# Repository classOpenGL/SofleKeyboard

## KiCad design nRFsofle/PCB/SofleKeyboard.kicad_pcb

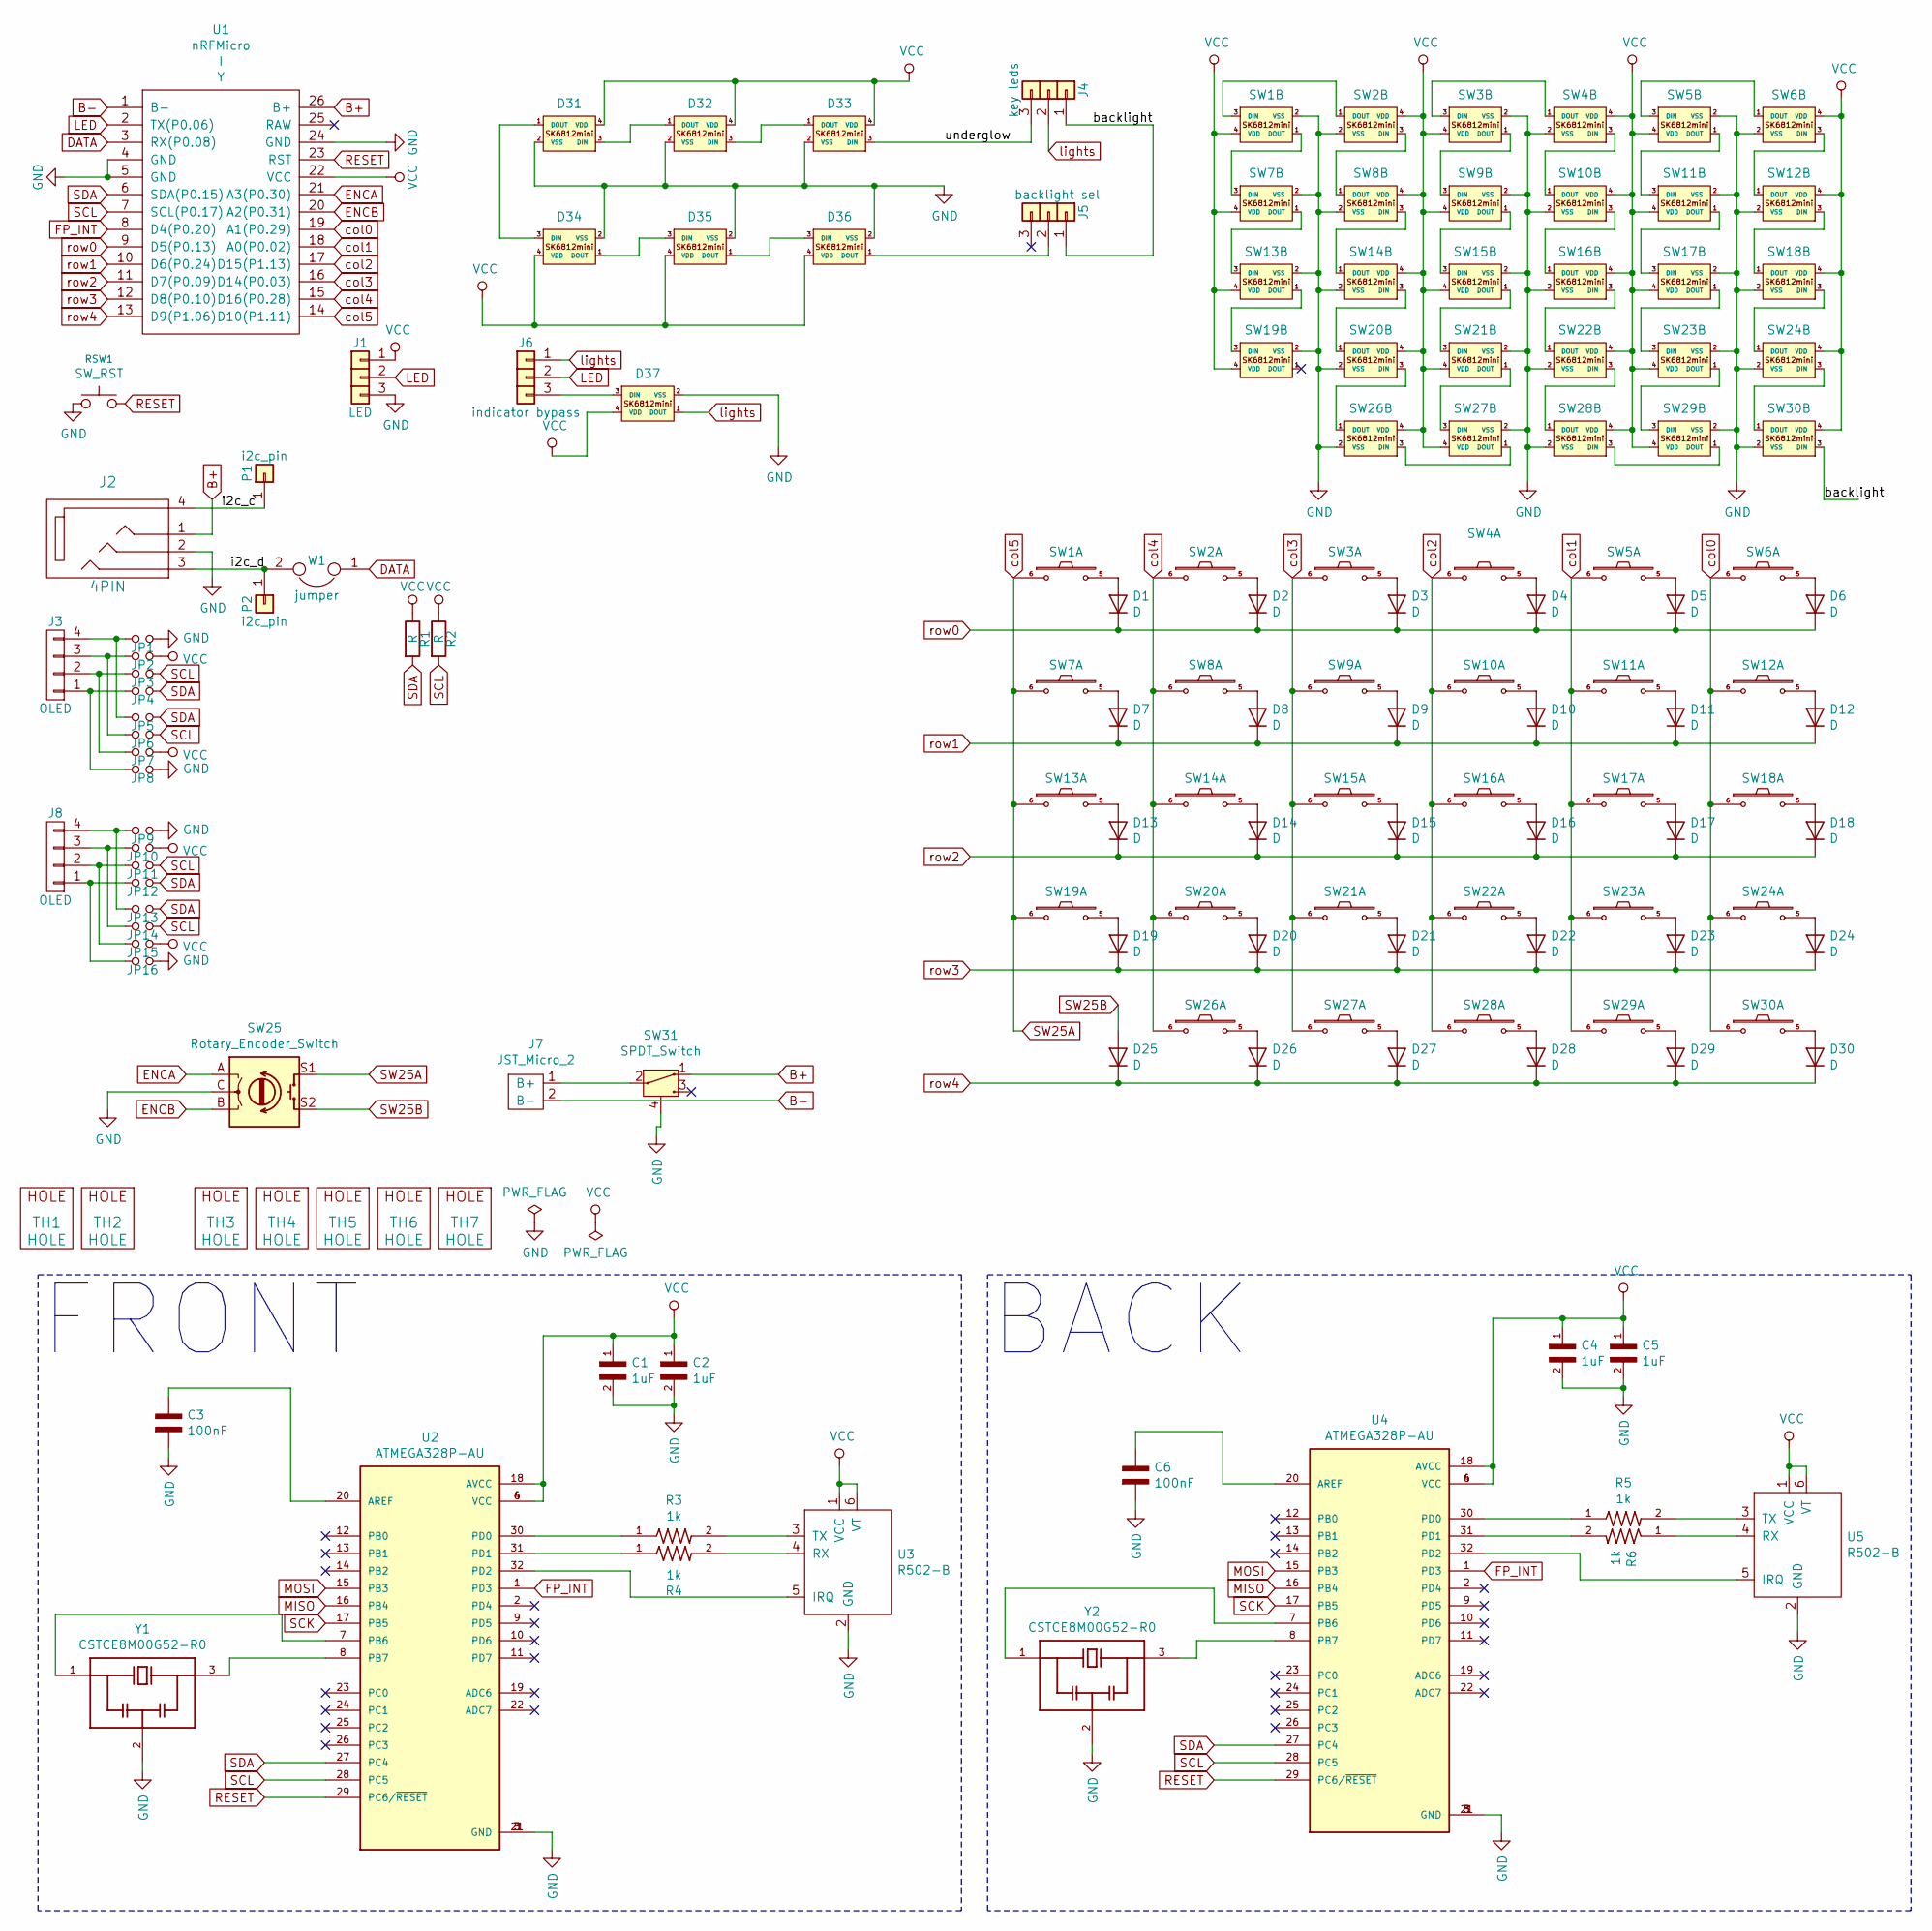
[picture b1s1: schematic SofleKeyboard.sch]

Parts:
C1, C2, C4, C5: 1uF
C3, C6: 100nF
D1, D2, D3, D4, D5, D6, D7, D8, D9, D10, D11, D12, D13, D14, D15, D16, D17, D18, D19, D20, D21, D22, D23, D24, D25, D26, D27, D28, D29, D30: D; crkbd-diode
D31, D32, D33, D34, D35, D36, D37: LED_sk2812_SM; SK6812MINI_underglow_dev
J1: LED
J2: 4PIN; MJ-4PP-9
J3, J8: OLED; OLED_4Pin
J4: key leds; 3x1header
J5: backlight sel; 3x1header
J6: indicator bypass; 3x1header
J7: JST_Micro_2
JP1, JP2, JP3, JP4, JP5, JP6, JP7, JP8, JP9, JP10, JP11, JP12, JP13, JP14, JP15, JP16: Jumper_NO_Small; Jumper
P1, P2: i2c_pin; 1pin_conn
R1, R2: R; RESISTOR_mini
R3, R4, R5, R6: 1k; Voltage_Rating 50 V; Tolerance .1%
RSW1: SW_RST; TACT_SWITCH_TVBP06
SW1, SW2, SW3, SW4, SW5, SW6, SW7, SW8, SW9, SW10, SW11, SW12, SW13, SW14, SW15, SW16, SW17, SW18, SW19, SW20, SW21, SW22, SW23, SW24, SW26, SW27, SW28, SW29, SW30: SW_PUSH-MX_W_LED; SK6812MINI_and_cherry
SW25: Rotary_Encoder_Switch; RotaryEncoder_Alps_EC11E-Switch_Vertical_H20mm-keebio_modif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
SW31: SPDT_Switch; EG1206A_Switch
TH1, TH2: HOLE; M2_HOLE_PCB
TH3, TH4, TH5, TH6, TH7: HOLE; HOLE_M2_TH
U1: nRFMicro; nRFMicro_1.4
U2, U4: ATMEGA328P-AU; QFP80P900X900X120-32N
U3, U5: R502-B
W1: jumper; jumper_data
Y1, Y2: CSTCE8M00G52-R0; OSC_CSTCE8M00G52-R0; PARTREV May 7, 2019

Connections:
/backlight: J4.1, J5.1, SW30.3 (DIN)
/i2c_c: J2.4, P1.1
/i2c_d: J2.3, P2.1, W1.2
/underglow: D33.3 (DIN), J4.3
B+: J2.1, SW31.1, U1.26 (B+)
B-: J7.2 (B-), U1.1 (B-)
DATA: U1.3 (RX(P0.08)), W1.1
ENCA: SW25.A, U1.21 (A3(P0.30))
ENCB: SW25.B, U1.20 (A2(P0.31))
FP_INT: U1.8 (D4(P0.20)), U2.1 (PD3), U4.1 (PD3)
GND: C1.2, C2.2, C3.1, C4.2, C5.2, C6.1, D31.2 (VSS), D32.2 (VSS), D33.2 (VSS), D34.2 (VSS), D35.2 (VSS), D36.2 (VSS), D37.2 (VSS), J1.3, J2.2, JP1.2, JP8.2, JP9.2, JP16.2, RSW1.1, SW1.2 (VSS), SW2.2 (VSS), SW3.2 (VSS), SW4.2 (VSS), SW5.2 (VSS), SW6.2 (VSS), SW7.2 (VSS), SW8.2 (VSS), SW9.2 (VSS), SW10.2 (VSS), SW11.2 (VSS), SW12.2 (VSS), SW13.2 (VSS), SW14.2 (VSS), SW15.2 (VSS), SW16.2 (VSS), SW17.2 (VSS), SW18.2 (VSS), SW19.2 (VSS), SW20.2 (VSS), SW21.2 (VSS), SW22.2 (VSS), SW23.2 (VSS), SW24.2 (VSS), SW25.C, SW26.2 (VSS), SW27.2 (VSS), SW28.2 (VSS), SW29.2 (VSS), SW30.2 (VSS), SW31.4, U1.4 (GND), U1.5 (GND), U1.24 (GND), U2.3 (GND), U2.5 (GND), U2.21 (GND), U3.2 (GND), U4.3 (GND), U4.5 (GND), U4.21 (GND), U5.2 (GND), Y1.2, Y2.2; also elsewhere on the board
LED: J1.2, J6.2, U1.2 (TX(P0.06))
MISO: U2.16 (PB4), U4.16 (PB4); also elsewhere on the board
MOSI: U2.15 (PB3), U4.15 (PB3); also elsewhere on the board
unnamed: C3.2, U2.20 (AREF)
unnamed: C6.2, U4.20 (AREF)
unnamed: D1.2 (A), SW1.5
unnamed: D2.2 (A), SW2.5
unnamed: D3.2 (A), SW3.5
unnamed: D4.2 (A), SW4.5
unnamed: D5.2 (A), SW5.5
unnamed: D6.2 (A), SW6.5
unnamed: D7.2 (A), SW7.5
unnamed: D8.2 (A), SW8.5
unnamed: D9.2 (A), SW9.5
unnamed: D10.2 (A), SW10.5
unnamed: D11.2 (A), SW11.5
unnamed: D12.2 (A), SW12.5
unnamed: D13.2 (A), SW13.5
unnamed: D14.2 (A), SW14.5
unnamed: D15.2 (A), SW15.5
unnamed: D16.2 (A), SW16.5
unnamed: D17.2 (A), SW17.5
unnamed: D18.2 (A), SW18.5
unnamed: D19.2 (A), SW19.5
unnamed: D20.2 (A), SW20.5
unnamed: D21.2 (A), SW21.5
unnamed: D22.2 (A), SW22.5
unnamed: D23.2 (A), SW23.5
unnamed: D24.2 (A), SW24.5
unnamed: D26.2 (A), SW26.5
unnamed: D27.2 (A), SW27.5
unnamed: D28.2 (A), SW28.5
unnamed: D29.2 (A), SW29.5
unnamed: D30.2 (A), SW30.5
unnamed: D31.1 (DOUT), D34.3 (DIN)
unnamed: D31.3 (DIN), D32.1 (DOUT)
unnamed: D32.3 (DIN), D33.1 (DOUT)
unnamed: D34.1 (DOUT), D35.3 (DIN)
unnamed: D35.1 (DOUT), D36.3 (DIN)
unnamed: D36.1 (DOUT), J5.2
unnamed: D37.3 (DIN), J6.3
unnamed: J3.1, JP4.1, JP8.1
unnamed: J3.2, JP3.1, JP7.1
unnamed: J3.3, JP2.1, JP6.1
unnamed: J3.4, JP1.1, JP5.1
unnamed: J7.1 (B+), SW31.2
unnamed: J8.1, JP12.1, JP16.1
unnamed: J8.2, JP11.1, JP15.1
unnamed: J8.3, JP10.1, JP14.1
unnamed: J8.4, JP9.1, JP13.1
unnamed: R3.1, U2.30 (PD0)
unnamed: R3.2, U3.3 (TX)
unnamed: R4.1, U2.31 (PD1)
unnamed: R4.2, U3.4 (RX)
unnamed: R5.1, U4.30 (PD0)
unnamed: R5.2, U5.3 (TX)
unnamed: R6.1, U5.4 (RX)
unnamed: R6.2, U4.31 (PD1)
unnamed: SW1.1 (DOUT), SW7.3 (DIN)
unnamed: SW1.3 (DIN), SW2.1 (DOUT)
unnamed: SW2.3 (DIN), SW8.1 (DOUT)
unnamed: SW3.1 (DOUT), SW9.3 (DIN)
unnamed: SW3.3 (DIN), SW4.1 (DOUT)
unnamed: SW5.3 (DIN), SW6.1 (DOUT)
unnamed: SW4.3 (DIN), SW10.1 (DOUT)
unnamed: SW10.3 (DIN), SW16.1 (DOUT)
unnamed: SW11.1 (DOUT), SW17.3 (DIN)
unnamed: SW5.1 (DOUT), SW11.3 (DIN)
unnamed: SW6.3 (DIN), SW12.1 (DOUT)
unnamed: SW12.3 (DIN), SW18.1 (DOUT)
unnamed: SW13.1 (DOUT), SW19.3 (DIN)
unnamed: SW7.1 (DOUT), SW13.3 (DIN)
unnamed: SW8.3 (DIN), SW14.1 (DOUT)
unnamed: SW14.3 (DIN), SW20.1 (DOUT)
unnamed: SW15.1 (DOUT), SW21.3 (DIN)
unnamed: SW9.1 (DOUT), SW15.3 (DIN)
unnamed: SW16.3 (DIN), SW22.1 (DOUT)
unnamed: SW17.1 (DOUT), SW23.3 (DIN)
unnamed: SW18.3 (DIN), SW24.1 (DOUT)
unnamed: SW20.3 (DIN), SW26.1 (DOUT)
unnamed: SW21.1 (DOUT), SW27.3 (DIN)
unnamed: SW22.3 (DIN), SW28.1 (DOUT)
unnamed: SW23.1 (DOUT), SW29.3 (DIN)
unnamed: SW24.3 (DIN), SW30.1 (DOUT)
unnamed: SW26.3 (DIN), SW27.1 (DOUT)
unnamed: SW28.3 (DIN), SW29.1 (DOUT)
unnamed: U2.7 (PB6), Y1.1
unnamed: U2.8 (PB7), Y1.3
unnamed: U2.32 (PD2), U3.5 (IRQ)
unnamed: U4.7 (PB6), Y2.1
unnamed: U4.8 (PB7), Y2.3
unnamed: U4.32 (PD2), U5.5 (IRQ)
RESET: RSW1.2, U1.23 (RST), U2.29 (PC6/~RESET), U4.29 (PC6/~RESET); also elsewhere on the board
SCK: U2.17 (PB5), U4.17 (PB5); also elsewhere on the board
SCL: JP3.2, JP6.2, JP11.2, JP14.2, R2.2, U1.7 (SCL(P0.17)), U2.28 (PC5), U4.28 (PC5)
SDA: JP4.2, JP5.2, JP12.2, JP13.2, R1.2, U1.6 (SDA(P0.15)), U2.27 (PC4), U4.27 (PC4)
SW25A: SW1.6, SW7.6, SW13.6, SW19.6, SW25.S1, U1.14 (D10(P1.11))
SW25B: D25.2 (A), SW25.S2
VCC: C1.1, C2.1, C4.1, C5.1, D31.4 (VDD), D32.4 (VDD), D33.4 (VDD), D34.4 (VDD), D35.4 (VDD), D36.4 (VDD), D37.4 (VDD), J1.1, JP2.2, JP7.2, JP10.2, JP15.2, R1.1, R2.1, SW1.4 (VDD), SW2.4 (VDD), SW3.4 (VDD), SW4.4 (VDD), SW5.4 (VDD), SW6.4 (VDD), SW7.4 (VDD), SW8.4 (VDD), SW9.4 (VDD), SW10.4 (VDD), SW11.4 (VDD), SW12.4 (VDD), SW13.4 (VDD), SW14.4 (VDD), SW15.4 (VDD), SW16.4 (VDD), SW17.4 (VDD), SW18.4 (VDD), SW19.4 (VDD), SW20.4 (VDD), SW21.4 (VDD), SW22.4 (VDD), SW23.4 (VDD), SW24.4 (VDD), SW26.4 (VDD), SW27.4 (VDD), SW28.4 (VDD), SW29.4 (VDD), SW30.4 (VDD), U1.22 (VCC), U2.4 (VCC), U2.6 (VCC), U2.18 (AVCC), U3.1 (VCC), U3.6 (VT), U4.4 (VCC), U4.6 (VCC), U4.18 (AVCC), U5.1 (VCC), U5.6 (VT); also elsewhere on the board
col0: SW6.6, SW12.6, SW18.6, SW24.6, SW30.6, U1.19 (A1(P0.29))
col1: SW5.6, SW11.6, SW17.6, SW23.6, SW29.6, U1.18 (A0(P0.02))
col2: SW4.6, SW10.6, SW16.6, SW22.6, SW28.6, U1.17 (D15(P1.13))
col3: SW3.6, SW9.6, SW15.6, SW21.6, SW27.6, U1.16 (D14(P0.03))
col4: SW2.6, SW8.6, SW14.6, SW20.6, SW26.6, U1.15 (D16(P0.28))
lights: D37.1 (DOUT), J4.2, J6.1
row0: D1.1 (K), D2.1 (K), D3.1 (K), D4.1 (K), D5.1 (K), D6.1 (K), U1.9 (D5(P0.13))
row1: D7.1 (K), D8.1 (K), D9.1 (K), D10.1 (K), D11.1 (K), D12.1 (K), U1.10 (D6(P0.24))
row2: D13.1 (K), D14.1 (K), D15.1 (K), D16.1 (K), D17.1 (K), D18.1 (K), U1.11 (D7(P0.09))
row3: D19.1 (K), D20.1 (K), D21.1 (K), D22.1 (K), D23.1 (K), D24.1 (K), U1.12 (D8(P0.10))
row4: D25.1 (K), D26.1 (K), D27.1 (K), D28.1 (K), D29.1 (K), D30.1 (K), U1.13 (D9(P1.06))

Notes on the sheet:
FRONT
BACK

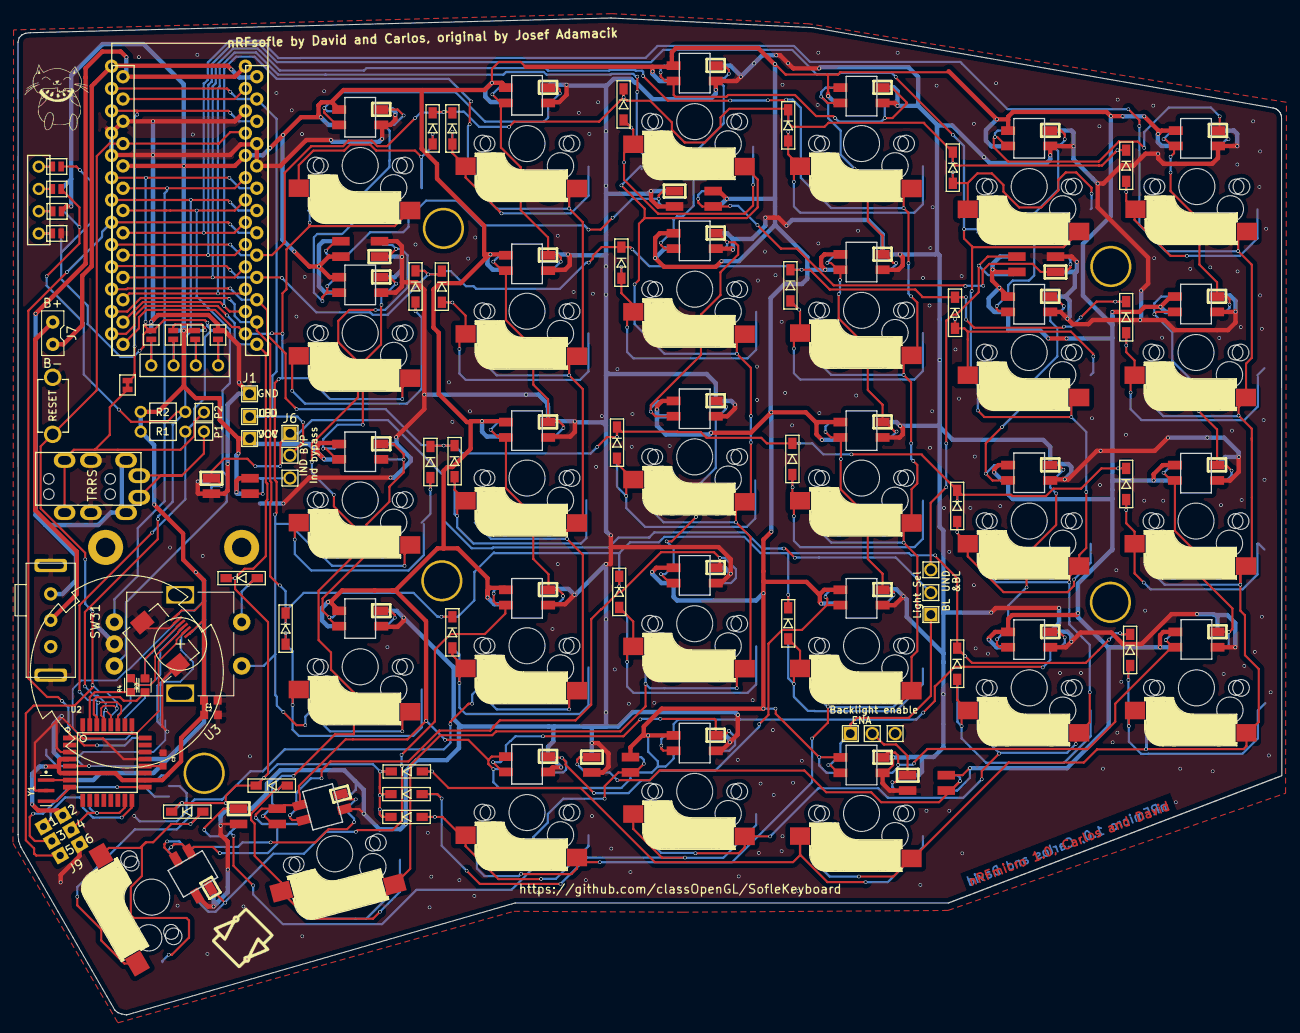
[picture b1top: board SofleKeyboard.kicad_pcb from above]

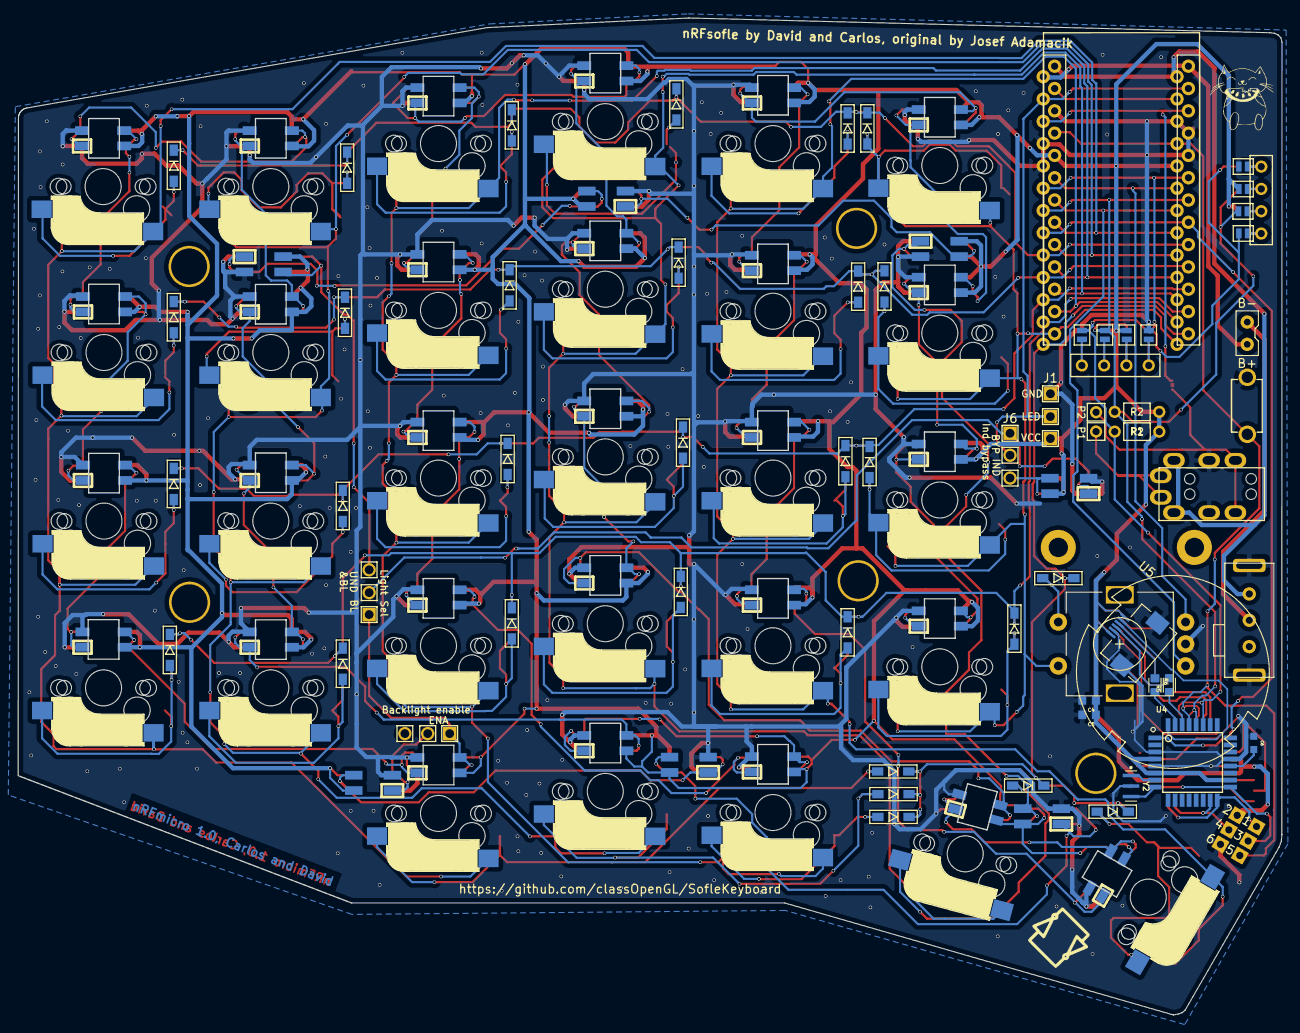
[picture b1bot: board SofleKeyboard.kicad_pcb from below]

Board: 2 copper layers, 143.9 x 113.6 mm, 125 parts (17 on the bottom side), 121 nets.

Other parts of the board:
J9: SPI_PADS
Ref**: Val**; Logo
Ref**#2: Val**; Logo

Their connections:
GND: J9.6; also elsewhere on the board
MISO: J9.1; also elsewhere on the board
MOSI: J9.4; also elsewhere on the board
RESET: J9.5; also elsewhere on the board
SCK: J9.3; also elsewhere on the board
VCC: J9.2; also elsewhere on the board

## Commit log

2021-09-15 Created nRFsofle base files
    This new keyboard origins from the Sofle RGB keyboard.
    New added features are:
    * Compatibility with nRFmicro 1.4 board
    * Battery connector
    * Switch for the battery
    * Added connector for 128x64 OLED display
2021-09-15 Updated repo url
    Now the repository URL printed in the silk layer is updated
    to this one.
2021-09-23 Added needed components for fingerprint sensor
    New components were added to the component list (symbols and footprints).
    All these components were taken from 'https://www.snapeda.com/', except
    for the fingerprint sensor.
    A summary of the new components of the nRFsofle compared to original Sofle RGB:
    Type | Component number | Purchase link
    _______________________________________________________________________________
2021-09-23 Implemented the schematic to add fingerprint sensor
    The implemented circuit is duplicated to put the circuit in both layers,
    so the board can be printed for both sides of the keyboard.
2021-10-01 Generated the PCB to add fingerprint sensor to the keyboard
    In order to add this new feature, a microcontroller was added.
    It is duplicated because this board can be used as left and
    right sides of the keyboard, so only one of the sides should
    be soldered.
    The Atmega microcontroller reads the fingerprint sensor using
    UART protocol while the nRFmicro reads the Arduino fingerprint
2021-10-01 Added SPI programmer port interface
    Pinout of this port is equal to the used by Arduino Nano
2021-10-04 Added a BOM list of the soldering components and others
    There are to new lists, one containing a BOM format list, and the other one
    containing links to purchase the rest of the products.
    You can load the BOM list automatically in LCSC page.
2021-10-05 Added more purchase links.
    Added purchase links for the pass-through and the screws.
2021-11-07 Added plates for bottom and top sides of the keyboard
    These plates are located into nRFsofle/case/<plate>
    The provided formats are three kinds:
    * 3D model:
    - Path: nRFsofle/case/<plate>/Model
    - Formats: .blend, .stl
    * PCB:
2022-03-31 Added 3D models for keyboard building
    Several models created with FreeCAD were added in order to
    be able to build the keyboard. These models are:
    * Fitgerprint support (bottom)
    * Fingerprint support (top)
    * Plate spacer (should be used in top plate)
    Both fingerprint supports are used together to keep the
